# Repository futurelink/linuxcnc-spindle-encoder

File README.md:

# Incremental encoder Modbus RTU interface

This device is an interface to read incremental encoder meanings with Modbus.
It supports encoders from 100 to 1000PPR and interpolate position up to 4 times, 
so maximum resolutuion is 4000PPR. 

It's tested on 1000PPR encoder and it reads correct values on about 1000RPMs on internal 8MHz
ATtiny2313 RC oscillator, and about 2000PPM on 16MHz crystal.

## What does it do?

This small attiny2313 module and LinuxCNC component allows you to connect almost any precision encoder into LinuxCNC
and it works even if it has no Z phase output.

It allows your lathe execute G33, G33.1 (synchronized motion) and G76 (threading) canned cycles and 
use G96 (constant surface speed) spindle control strategy.

## Modbus

Device has slave ID 0x85. There are 6 16bit analog registers starting from reference address 0x00,
containing (0)heartbeat, (1)current position, (2)position increment, (3)current speed in RPM, (4)current Z-index value
and (5)encoder direction.

Device UART speed is 38400bps.

## Connection to LinuxCNC

Go to ./linuxcnc and execute:

```
$ sudo make
```

This will install component into your LinuxCNC.

Then you need this component in your HAL:

```
loadrt spindle_encoder
addf spindle-encoder.0 servo-thread
setp spindle-encoder.0.ppr 4096
net spindle-heartbeat  spindle-encoder.0.heartbeat <= mb2hal.spindle-encoder.heartbeat.int
net spindle-pos-in     spindle-encoder.0.pos-in <= mb2hal.spindle-encoder.pos-in.float
net spindle-pos-out    spindle-encoder.0.pos-out => motion.spindle-revs
net spindle-speed-rpm  spindle-encoder.0.speed-rpm <= mb2hal.spindle-encoder.speed-rpm.int
net spindle-speed      spindle-encoder.0.speed-rps => motion.spindle-speed-in
net spindle-index      spindle-encoder.0.index-in <= mb2hal.spindle-encoder.index.int
net spindle-index-ena  spindle-encoder.0.index-enable <=> motion.spindle-index-enable
net spindle-dir        spindle-encoder.0.direction <= mb2hal.spindle-encoder.direction.int
```

Also you'll need to load mb2hal module into userspace:

```
loadusr -W mb2hal config=modbus_config.ini
```

Copy modbus_config.ini from ./linuxcnc into your lathe configuration directory. Write your serial 
port device to SERIAL_PORT option in that ini file. Correct SERIAL_DELAY_MS if you need.

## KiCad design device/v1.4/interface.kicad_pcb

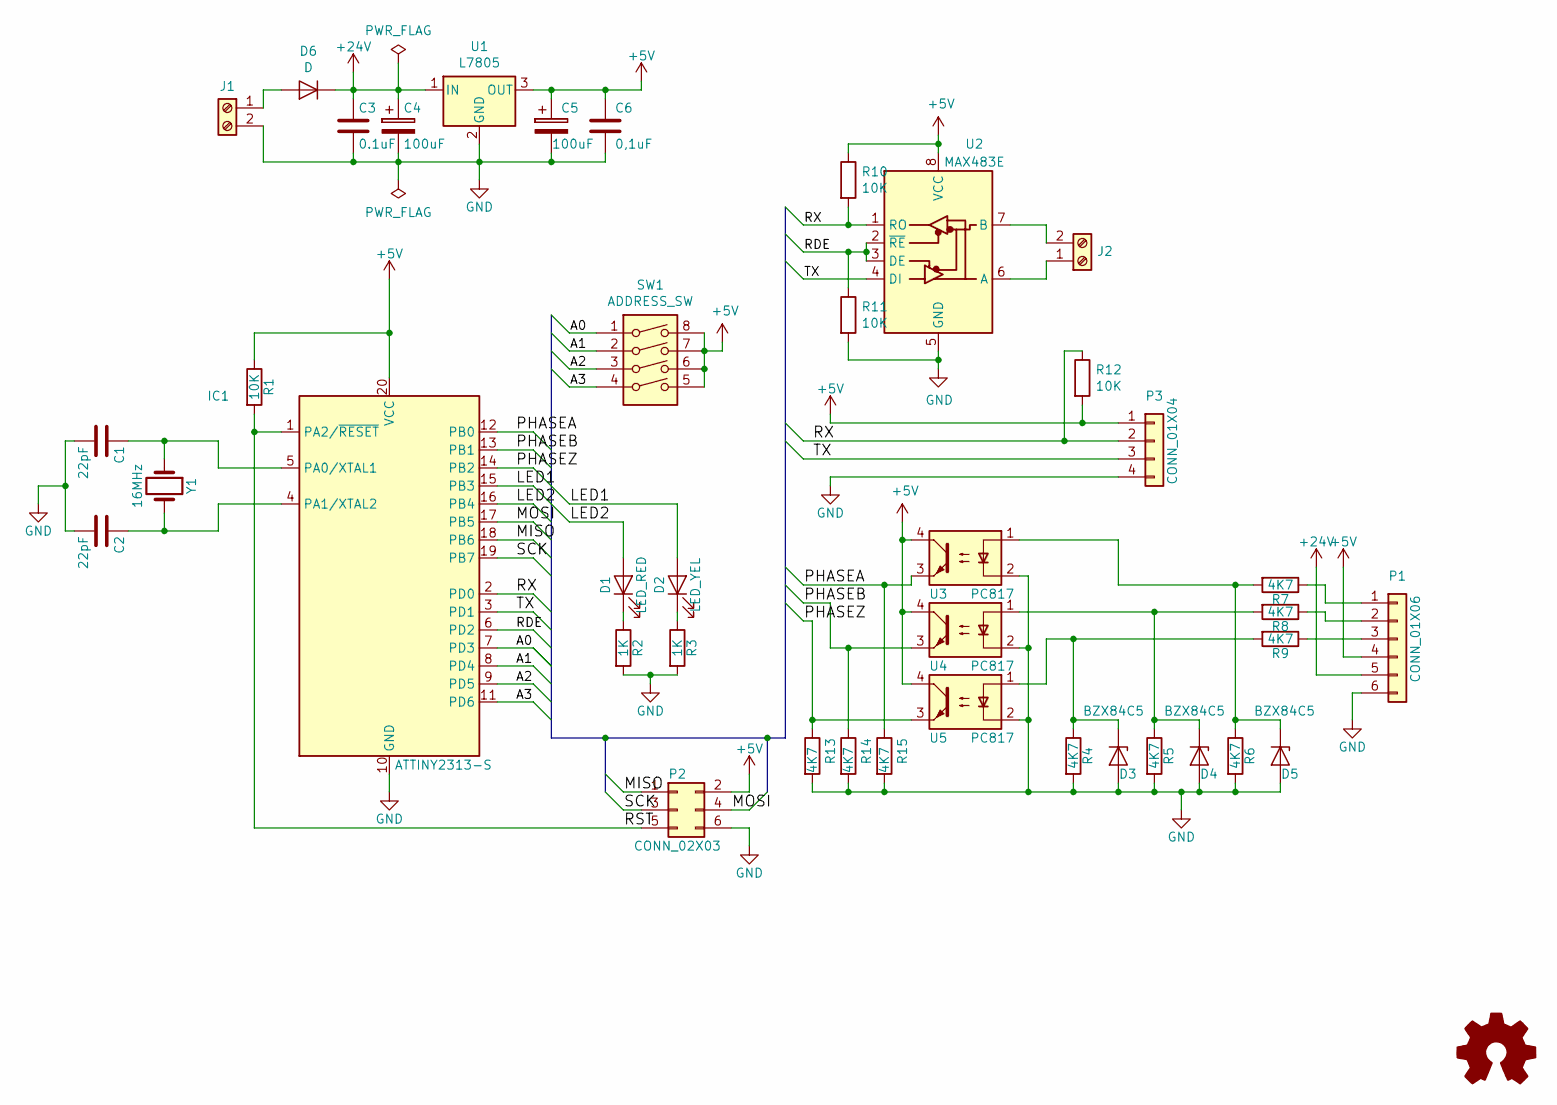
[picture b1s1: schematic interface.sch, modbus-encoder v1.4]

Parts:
C1, C2: 22pF; C_0805_2012Metric
C3: 0.1uF; C_0805_2012Metric
C4: 100uF; CP_Elec_8x10.5
C5: 100uF; CP_Elec_6.3x5.3
C6: 0,1uF; C_0805_2012Metric
D1: LED_RED; LED_1206_3216Metric
D2: LED_YEL; LED_1206_3216Metric
D3, D4, D5: BZX84C5; D_SOT-23_ANK
D6: D; D_1206_3216Metric
IC1: ATTINY2313-S; SOIC-20W_7.5x12.8mm_P1.27mm
J1: Screw_Terminal_1x02; TerminalBlock_bornier-2_P5.08mm
J2: Screw_Terminal_01x02; TerminalBlock_bornier-2_P5.08mm
P1: CONN_01X06; JST_XH_S6B-XH-A_1x06_P2.50mm_Horizontal
P2: CONN_02X03; PinHeader_2x03_P2.54mm_Vertical
P3: CONN_01X04; JST_XH_S4B-XH-A_1x04_P2.50mm_Horizontal
R1, R10, R11, R12: 10K; R_0805_2012Metric
R2, R3: 1K; R_0805_2012Metric
R4, R5, R6, R7, R8, R9, R13, R14, R15: 4K7; R_0805_2012Metric
SW1: ADDRESS_SW; SW_DIP_SPSTx04_Slide_9.78x12.34mm_W7.62mm_P2.54mm
U1: L7805; TO-252-2
U2: MAX483E; SOIC-8_3.9x4.9mm_P1.27mm
U3, U4, U5: PC817; DIP-4_W7.62mm_SMDSocket_SmallPads
Y1: 16MHz; Crystal_SMD_5032-2Pin_5.0x3.2mm

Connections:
+5V: C5.1, C6.1, IC1.20 (VCC), P1.4, P2.2, P3.1, R1.1, R10.1, R12.2, SW1.5, SW1.6, SW1.7, SW1.8, U1.3 (OUT), U2.8 (VCC), U3.4, U4.4, U5.4
+24V: C3.1, C4.1, D6.1 (K), P1.5, U1.1 (IN)
/A0: IC1.7 (PD3), SW1.1
/A1: IC1.8 (PD4), SW1.2
/A2: IC1.9 (PD5), SW1.3
/A3: IC1.11 (PD6), SW1.4
/LED1: D2.2 (A), IC1.15 (PB3)
/LED2: D1.2 (A), IC1.16 (PB4)
/MISO: IC1.18 (PB6), P2.1
/MOSI: IC1.17 (PB5), P2.4
/PHASEA: IC1.12 (PB0), R15.1, U3.3
/PHASEB: IC1.13 (PB1), R14.1, U4.3
/PHASEZ: IC1.14 (PB2), R13.1, U5.3
/RDE: IC1.6 (PD2), R11.1, U2.2 (~RE), U2.3 (DE)
/RST: IC1.1 (PA2/~RESET), P2.5, R1.2
/RX: IC1.2 (PD0), P3.2, R10.2, R12.1, U2.1 (RO)
/SCK: IC1.19 (PB7), P2.3
/TX: IC1.3 (PD1), P3.3, U2.4 (DI)
GND: C1.2, C2.2, C3.2, C4.2, C5.2, C6.2, D3.2 (A), D4.2 (A), D5.2 (A), IC1.10 (GND), J1.2, P1.6, P2.6, P3.4, R2.2, R3.2, R4.2, R5.2, R6.2, R11.2, R13.2, R14.2, R15.2, U1.2 (GND), U2.5 (GND), U3.2, U4.2, U5.2
unnamed: C1.1, IC1.5 (PA0/XTAL1), Y1.1
unnamed: C2.1, IC1.4 (PA1/XTAL2), Y1.2
unnamed: D1.1 (K), R2.1
unnamed: D2.1 (K), R3.1
unnamed: D3.1 (K), R4.1, R9.2, U5.1
unnamed: D4.1 (K), R5.1, R8.2, U4.1
unnamed: D5.1 (K), R6.1, R7.2, U3.1
unnamed: D6.2 (A), J1.1
unnamed: J2.1, U2.6 (A)
unnamed: J2.2, U2.7 (B)
unnamed: P1.1, R7.1
unnamed: P1.2, R8.1
unnamed: P1.3, R9.1

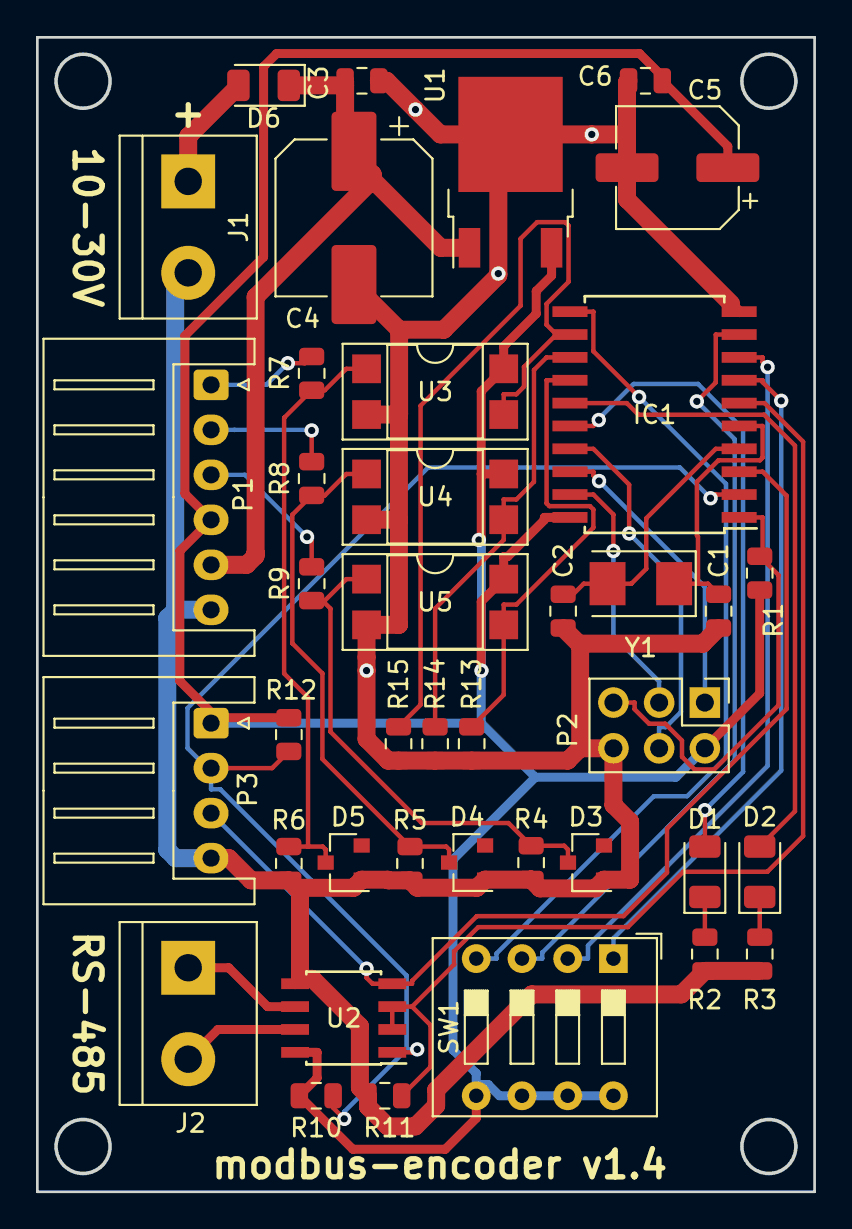
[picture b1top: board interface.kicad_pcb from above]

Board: 2 copper layers, 43.1 x 64.1 mm, 40 parts (0 on the bottom side), 32 nets.

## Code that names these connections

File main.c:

/*

Copyright 2019 Pavlov Denis <futurelink.vl@gmail.com>

This is free software: you can redistribute it and/or modify
it under the terms of the GNU General Public License as published by
the Free Software Foundation, either version 3 of the License, or
(at your option) any later version.

It is distributed in the hope that it will be useful,
but WITHOUT ANY WARRANTY; without even the implied warranty of
MERCHANTABILITY or FITNESS FOR A PARTICULAR PURPOSE.  See the
GNU General Public License for more details.

You should have received a copy of the GNU General Public License
along with this project.  If not, see <http://www.gnu.org/licenses/>.

*/

#include <avr/wdt.h>
#include <avr/io.h>
#include <avr/interrupt.h>

#include "config.h"

#define PARITY_NONE	0
#define PARITY_ODD	1
#define PARITY_EVEN	2

static void initPorts(void);
static void initUSART(uint8_t parity);
static void initTimer1(uint8_t timeout50usTicks);
static void initTimer0(void);

extern uint8_t slaveAddr;
extern volatile uint8_t sentLength;
extern volatile uint8_t sendLength;
extern uint8_t sendBuffer[];

int main(void) {
    asm("WDR");
    MCUSR &= ~(1 << WDRF);
    WDTCSR |= (1 << WDCE) | (1 << WDE);
    WDTCSR = (1 << WDE) | (1 << WDP2) | (1 << WDP1); // Вотчдог через 1 сек

    initUSART(PARITY_NONE);
    initTimer1(35);
    initTimer0();
    initPorts();

    sei();

    PORTB |= (1 << RED_LED); // Индикатор включения
    while (1) asm volatile("nop" ::);

    return 0;
}

void initPorts() {
    GIMSK |= (1 << PCIE);					// Разрешаем прерывания PCINT
    PCMSK |= (1 << PCINT2) | (1 << PCINT1) | (1 << PCINT0);	// Срабатывает на PCINT0, PCINT1 и PCINT2
    DDRB = (1 << RED_LED) | (1 << YELLOW_LED);			// Выходы на индикацию
    DDRD |= (1 << PD2);		// MAX483 чтение-запись
    PORTD &= ~(1 << PD2);	// MAX483 на чтение
    PORTD |= (1 << PD6) | (1 << PD5) | (1 << PD4) | (1 << PD3);

    // Считаем смещение адреса слейва
    slaveAddr = SLAVE_ID + ((PIND & (1 << PD6) & (1 << PD5) & (1 << PD4) & (1 << PD3)) >> PD3);
}

void initUSART(uint8_t parity) {
    UBRRH = UBRRH_VALUE;
    UBRRL = UBRRL_VALUE;
    UCSRB |= ((1 << TXEN) | (1 << RXEN) | (1 << RXCIE));	// Включаем прием, передачу и прерывание по приему
    UCSRC |= ((1 << UCSZ0) | (1 << UCSZ1));			// 8 бит данных (может будет убрать, т.к. по-умолчанию)

    // Настройка четности
    switch (parity) {
        case PARITY_EVEN: UCSRC |= (1 << UPM1); break;
        case PARITY_ODD: UCSRC |= (1 << UPM1) | (1 << UPM0); break;
        case PARITY_NONE: break;
    }
}

// Инициализация таймера тишины, таймер должен срабатывать после определенного
// интервала, но после приема каждого байта зануляться. По нему определяется
// конец посылки от мастера. Сразу не запускаем, он запускается по приему байта.
// -----------------------------------------------------------------------------
// Таймаут задается параметром в 50-миллисекундных интервалах.
void initTimer1(uint8_t timeout50usTicks) {
    OCR1A = (TIMER1_FREQ * timeout50usTicks) / (TIMER1_50US_TICKS);
    TCCR1A = 0;
    TCCR1B = (1 << CS12) | (1 << CS10); // Делитель 1024
    TCCR1C = 0;
    TCNT1 = 0;				// Сбрасываем счетчик
    TIMSK |= (1 << OCIE1A);		// Разрешаем прерывание TIMER1_COMPA_vect
}

// Инициализация таймера счета скорости, таймер на 20мс (0.02с). Считает кол-во меток,
// проходящих за период, чтобы определить скорость вращения энкодера.
void initTimer0() {
    // Таймер восьмибитный, поэтому OCR0A не более 255 должен быть
    OCR0A =  (TIMER0_FREQ * TIMER0_PERIOD_MS) / 1000; // При 16мс это работает нормально.
    TCCR0A = 0;
    TCCR0B = (1 << CS02) | (1 << CS00); // Делитель 1024 при 8МГц T = 128мкс, при 16МГц T = 64мкс
    TCNT0 = 0;				// Сбрасываем счетчик
    TIMSK |= (1 << OCIE0A);		// Разрешаем прерывание TIMER1_COMPA_vect
}

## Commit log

2019-09-08 readme
2019-09-08 added schematic pdf
2019-09-09 optimization
2019-09-09 optimized some elements
2019-09-09 improved PCINT_vect
2019-09-09 some improvements
2019-09-09 comments
2019-09-09 pin names in mb2hal
2019-09-12 16mhz crystal upgrade
2019-09-12 improvements
2019-09-13 device schematics and PCB
2019-09-13 remove ignored files
2019-09-13 pcb update
2019-09-13 added address switch
2019-09-13 render
2019-09-14 settings register work
2019-09-14 register reorganization
2019-09-14 some changes
2019-09-14 remove elf
2019-09-14 some optimization
2019-09-17 uart pull uo
2019-09-21 watchdog
2019-09-21 rs-485 support
2019-09-21 rs485 support
2019-09-21 pcb fix
2019-09-21 ignore
2019-10-16 fixed Zener BZX84
2019-10-25 added optocouplers
2019-10-25 gerbers
2019-10-27 fill zone
